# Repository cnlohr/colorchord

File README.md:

ColorChord
==========

Table of Contents
-----------------

- [ColorChord](#colorchord)
  - [Table of Contents](#table-of-contents)
  - [What is ColorChord?](#what-is-colorchord)
  - [Background](#background)
  - [Current State of Affairs](#current-state-of-affairs)
  - [ColorChord: Embedded](#colorchord-embedded)
- [Build Instructions](#build-instructions)
  - [Building ColorChord Embedded](#building-colorchord-embedded)
  - [Building with Linux](#building-with-linux)
  - [Building with Windows](#building-with-windows)
    - [clang](#clang)
    - [TCC](#tcc)
    - [MSYS2](#msys2)
  - [Using](#using)
  - [Additional Videos](#additional-videos)

What is ColorChord?
-------------------

Chromatic Sound to Light Conversion System.  It's really that simple.  Unlike so many of the sound responsive systems out there, ColorChord looks at the chromatic properties of the sound.  It looks for notes, not ranges.  If it hears an "E" it doesn't care what octave it's in, it's an E.  This provides a good deal more interesting patterns between instruments and music than would be available otherwise.

Background Video here:

ColorChord on an ESP8266:

More videos below!

Background
----------

Developed over many years, ColorChord 2 is now at the alpha stages.  ColorChord 2 uses the same principles as ColorChord 1.  A brief writeup on that can be seen here: http://cnlohr.blogspot.com/2010/11/colorchord-sound-lighting.html

The major differences in ColorChord 2 is the major rewrite to move everything back to the CPU and a multitude of algorithmic optimizations to make it possible to run on something other than the brand newest of systems.

Feuge in D Minor (ColorChord 2 running a strip of WS2812 LEDs):

ColorChord 2 running a voronoi diagram with Mayhem's Dr. Rocker

Current State of Affairs
------------------------

Currently, ColorChord 2 is designed to run on Linux or Windows.  It's not particularly tied to an architecture, but does pretty much need a dedicated FPU to achieve any decent performance.  Right now there aren't very many output options available for it.  The most interesting one used for debugging is a voronoi-diagram-like thing called "DisplayShapeDriver."

ColorChord: Embedded
--------------------

There is work on an embedded version of ColorChord, which avoids floating point operations anywhere in the output pipeline.  Though I have made efforts to port it to AVRs, it doesn't seem feasable to operate on AVRs without some shifty tricks which I'd like to avoid, so I have retargeted my efforts to 32-bit systems, such as the STM32F303, STM32F407, and (somehow) the ESP8266.  ColorChord Embedded uses a different codebase, located in the [embeddedcommon](/embeddedcommon) and distributed among the various embedded* folders.

Build Instructions
==================

Building ColorChord Embedded
----------------------------

The embedded version of Colorchord has a different build system than the desktop versions of Colorchord. See the build instructions for each of the supported embedded architectures in their respective folders

- [esp8266](embedded8266/README.md#build-instructions)
- [stm32f303](embeddedstm32f303/README.md)
- [stm32f407](embeddedstm32f407/) - TODO Add readme

Building with Linux
-----------------
From the linux terminal use `apt-get` to install the following packages for Debian/Ubuntu/Mint:
```
apt-get install build-essential libpulse-dev libasound2-dev libx11-dev libxext-dev libxinerama-dev libusb-1.0-0-dev libudev-dev
```

To get colorchord, type:

```
git clone --recurse-submodules https://github.com/cnlohr/colorchord
```
This will download the colorchord source code into the colorchord directory

You really want to be using colorchord2, so we need to move to it's build directory to compile the source code.
```
cd colorchord/colorchord2
```
To make colorchord, type:

```
make
```
Building with Windows
-------------------

There are 3 options available for building on Windows, clang, or TCC, MSYS2.
### clang
Start by [downloading](https://clang.llvm.org/) the clang compiler, and installing it.
You can also install using `winget` using the following command in PowerShell
```
winget install -e --id LLVM.LLVM
```

If you have the Windows SDK installed, you should not need to do any additional work.  
If you do not, you'll want to either [install it](https://developer.microsoft.com/en-US/windows/downloads/windows-11-sdk/) to get the official headers. Realistically, it's easyist to get the headers by installing Visual Studio Communitiy and selecting the C/C++ Desktop Application devlopment package and installing it from there [Visual Studio](https://visualstudio.microsoft.com/).

Once the Windows headers are installed run the clang batch script, and it should output to `colorchord2/colorchord.exe`.
```
./compile-clang.bat
```

### TCC
Start by [downloading TCC](http://savannah.nongnu.org/projects/tinycc/), and extracting it to `C:\tcc`.
You can put it anywhere you like, but the compile script defaults to this location. If you install 
to the default location, you can skip the next step.

Edit the batch script at `colorchord2/windows/compile.bat`:
- Edit line 17 (`CC`) to be the location where you put TCC. If there are spaces in the path, wrap the entire path in quotes.

Note that TCC is not able to use the Windows SDK, and as such using the unofficial headers is required, and automatically enabled when compiling with TCC. If you encounter issues, try the clang method above instead. TCC does not support open-gl rendering and is limited to software rendering.

### MSYS2
With either 64bit or 32bit [MSYS2](https://msys2.github.io/) installed, run the _MSYS2 MSYS_ launcher and use `pacman` to set up a MinGW32 toolchain, if you don't have one already:
```
pacman -S mingw-w64-i686-toolchain
```
If you see "`/mingw32 exists in filesystem`", you must temporarily rename or relocate the _mingw32.exe_ file at MSYS2's root folder level and try again. Restore _mingw32.exe_ before moving on.

Next, run the _MSYS2 MinGW 32bit_ launcher to access the toolchain. The previously launched _MSYS_ terminal can be closed.

To make colorchord, navigate to your working copy and type:
```
mingw32-make colorchord.exe
```

Using
-----

To run colorchord, use the following syntax:

```
./colorchord [config file, by default 'default.conf'] [any additional parameters]
```

If you edit default.conf while the program is running and resave it, it will use the settings in the newly saved file.

Note that the colorchord executable file is located in the colorchord2 directory in the colorchord repository. 

Additional Videos
-----------------

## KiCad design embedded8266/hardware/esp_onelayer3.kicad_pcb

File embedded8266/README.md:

#ESP8266 ColorChord

## WARNING THIS IS UNDER CONSTRUCTION

(based off of ESP8266 I2S WS2812 Driver)

This project is based off of the I2S interface for the mp3 player found here:
https://github.com/espressif/esp8266_mp3_decoder/

If you want more information about the build environment, etc.  You should
check out the regular WS2812 driver, found here: https://github.com/cnlohr/esp8266ws2812i2s

WARNING: This subproject is very jankey!  It's about stable, but I don't think it's quite there yet.

## Hardware Connection

Unfortunately the I2S Out (WS2812 in) pin is the same as RX1 (pin 25), which means if you are programming via the UART, it'll need to be unplugged any time you're testing.  The positive side of this is that it is a pin that is exposed on most ESP8266 breakout boards.

The audio data is taken from TOUT, but must be kept between 0 and 1V.

An option that has been thoroughly tested is for use with the 2019 MAGFest Swadge.  https://github.com/cnlohr/swadge2019

Audio portion:

## Notes

./makeconf.inc has a few variables that Make uses for building and flashing the firmware.
Most notably the location of the toolchain for the esp8266/85 on your system.
You should edit them according to your preferences or better add `export ESP_ROOT='/path/to/the/esp-open-sdk'` to your bashrc.

If you have problems with burning the firmware or transfering page data over network (`make netburn` or `make netweb`), you should try uncommenting

    OPTS += -DVERIFY_FLASH_WRITE

in `makeconf.inc`. This way the esp checks if the flash is written correctly.
Especially with some ESP-01 modules there has been a problem with the flash
not being written correctly.

## Build Instructions

To build colorchord for the esp8266, you first must install the development tools for the esp8266 so that you can compile the code and flash it to the device.

### Setup Toolchain
Follow the instructions in Charles' getting started video to install the toolchain (up until about 3:30 into the video).

The instructions shown in the video are from the [esp82xx repo](https://github.com/cnlohr/esp82xx) on github.

TLDR version: You should really watch the video and look at the other instructions though.
1. if you are on Windows you need to install WSL1 (Windows Subsystem for Linux version 1). 
2. Install Python2 and Make
3. Install pip (for Python 2)
4. Install pyserial (for Python 2)
5. Install Charles' prepackaged toolchain to the `~/esp8266` directory (`esp8266` directory in your home folder).
6. Set the `ESP_ROOT` environment variable in your `.profile` or `.bashrc` file. Check to see if one of these files exist (they are hidden by default), if one of them does exist, edit it adding the following line to the file.
```
export ESP_ROOT=$(HOME)/esp8266/esp-open-sdk
```

### Build Colorchord Embedded
At this point you should have your development toolchain set up, now we will download and install colorchord.

Start by cloning this git repository, in a terminal window use the command
```
git clone https://github.com/cnlohr/colorchord.git --recurse-submodules
```
This will download the source code for colorchord and all of its dependencies.

Next, move to the `embedded8266` directory so that we can compile the version of colorchord for the esp8266.
```
cd colorchord/embedded8266
```

Now we will need to build colorchord, this step will need to be done if you make any changes to the colorchord code.
```
make all
```
Hopefully the previous command completed without errors, if it did not, please refer to the [common problems](#common-problems) section. If all went well, there should be three binary files in your build directory `image.elf`, `image.elf-0x00000.bin`, and `image.elf-0x10000.bin`. You can check this with the command
```
ls -l image.elf*
```

### Flash to the ESP8266
Before flashing the program to the esp8266 it must be connected to the computer over a usb-to-serial connection and the correct port on the computer must be known. If using Windows (WSL) this will be the COM port shown by Windows Device Manager. For example, `COM4` in Windows will refer to `/dev/ttyS4` in WSL (See [2:35](https://youtu.be/LiKNRBIcGII?t=155) from the previously mentioned video). On a Linux machine it will most likely be `/dev/ttyUSB0`. The file determined here will specify the `PORT` value in later commands, so if you had `COM4`, then `PORT` would be `/dev/ttyS4`.

If this is your first time using the esp8266 module with colorchord run the following command.
```
PORT=<port value> make erase
PORT=<port value> make burnitall
```
These two commands erase the contents of esp8266 memory and flash the program (and some base files) to it.

If you have made some changes to colorchord and you want to test them use the command
```
PORT=<port_value> make burn
```
### Connect to the ESP8266
If all went well, the esp module should be broadcasting a wifi access point that you can connect to. Once that is done, you should be able to see the colorchord webpage dashboard at the ip address [192.168.4.1](http://192.168.4.1). That should be it! Enjoy using colorchord, and don't hesitate to reach out if you have any issues.

## Common Problems

**Under Construction**

If you experience any issues building colorchord embedded, please open an issue and we will try and work through it. I will try and keep this section up to date with relevant information.

**WSL Path Issues** 
Under WSL the default Windows environment paths are included. When building colorchord and the Windows User/System Path includes non Linux compatible characters (eg. spaces and parentheses like /Program Files (x86)) it will fail compililng.
An easy solution is to backup the Windows path variable, then deleting keys including spaces and parentheses and restarting WSL.

**Flash tool not using specified port**
WSL sometimes doesn't correctly use the environment variable that specifies the serial port. It needs to be changed in the user.cfg file in the /embedded8266 folder.

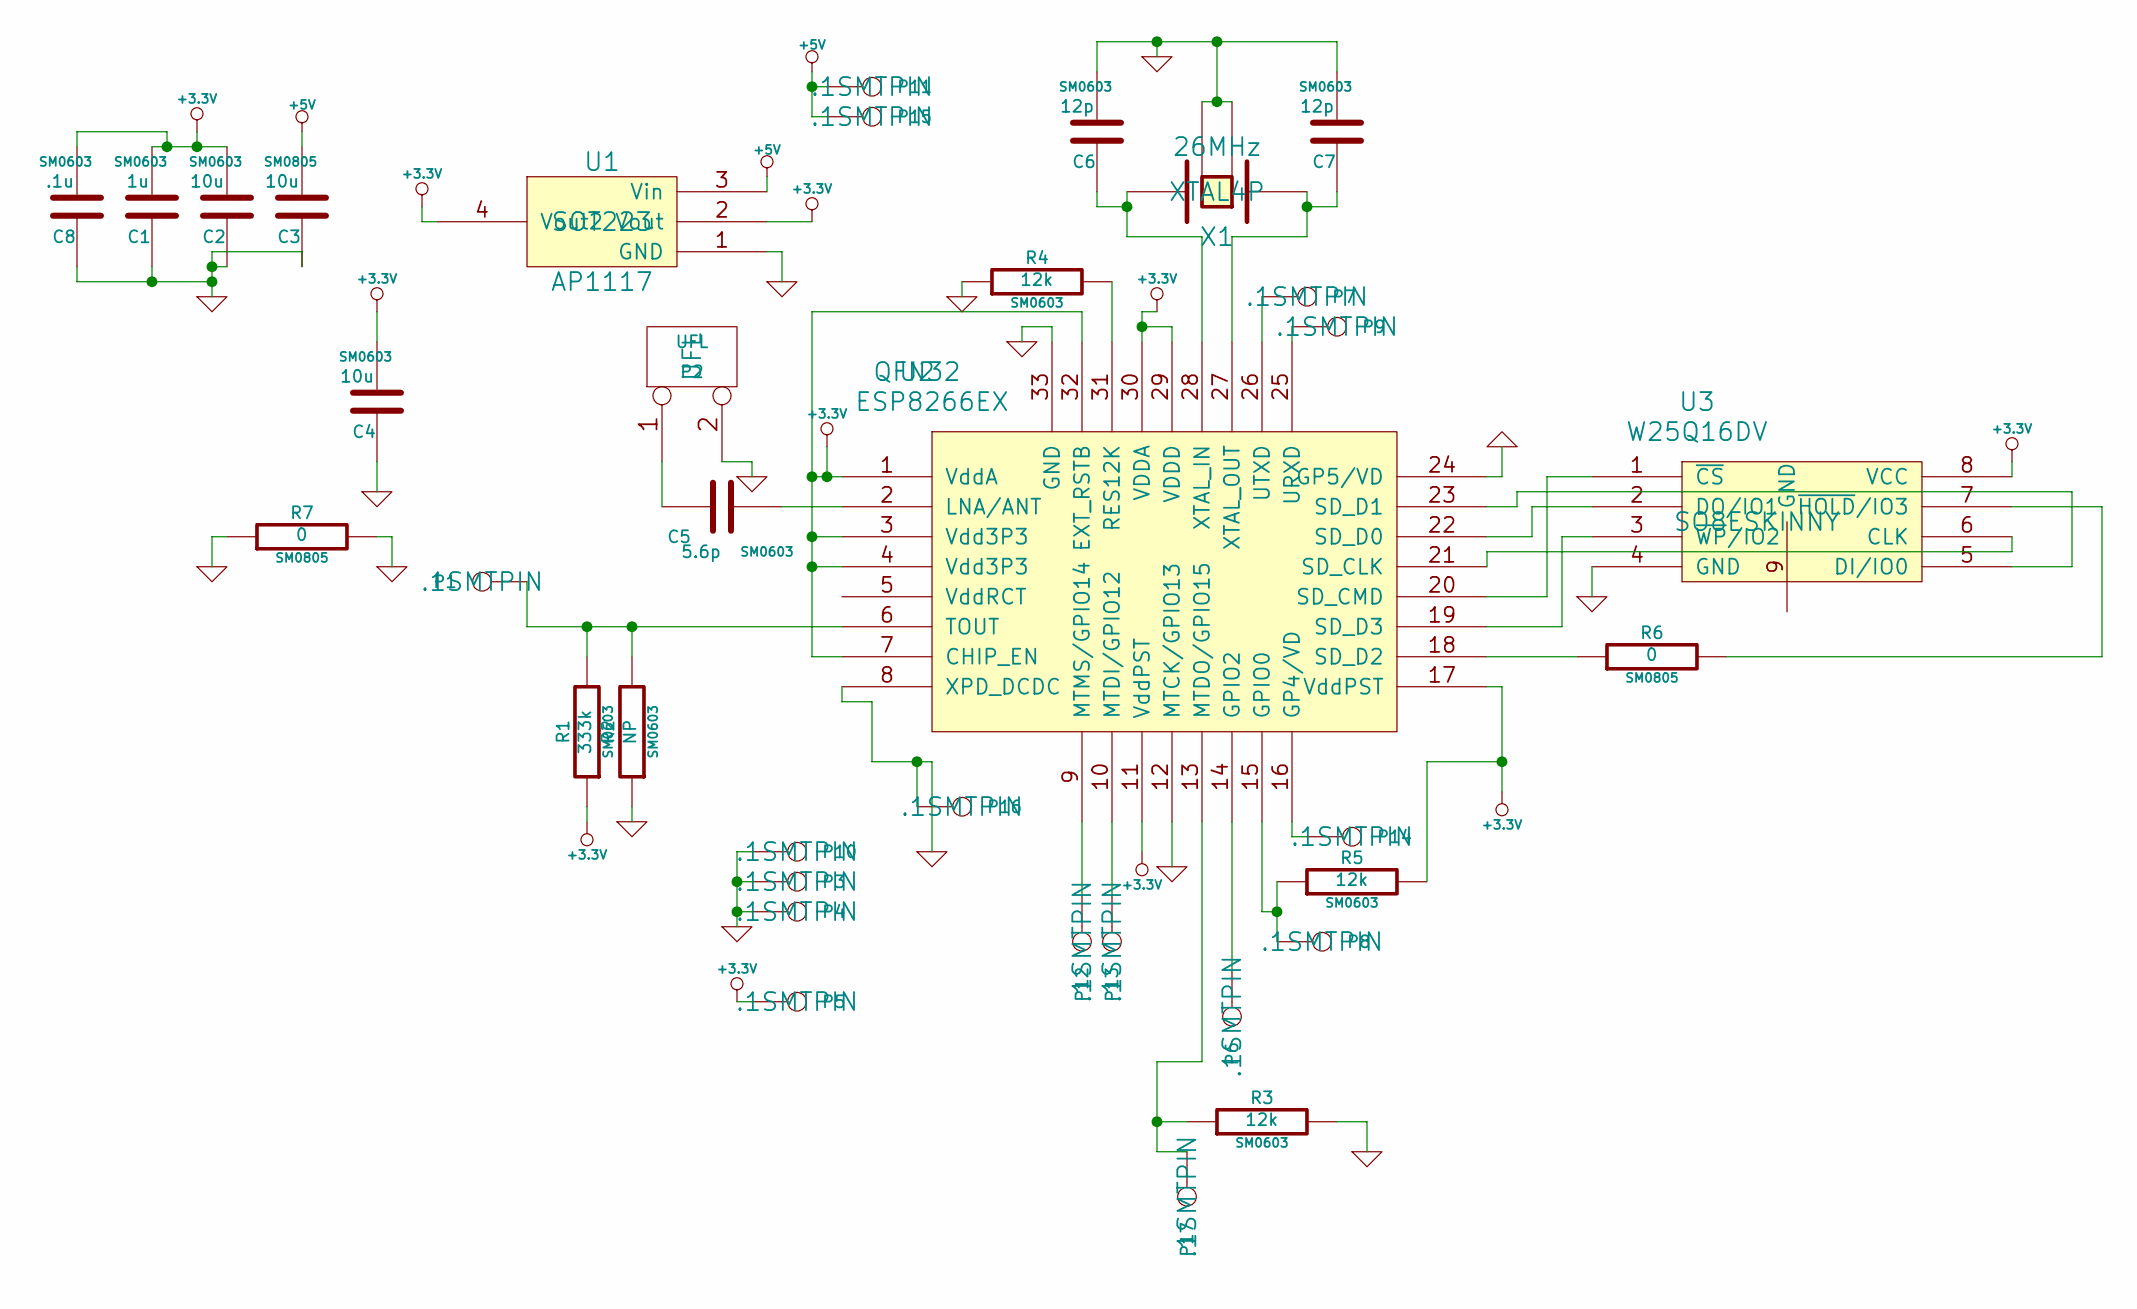
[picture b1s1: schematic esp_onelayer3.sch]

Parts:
C1: 1u; SM0603
C2, C4: 10u; SM0603
C3: 10u; SM0805
C5: 5.6p; SM0603
C6, C7: 12p; SM0603
C8: .1u; SM0603
P1: MIC; .1SMTPIN
P2: UFL
P3, P4, P10, P16: GND; .1SMTPIN
P5, P11, P15: 5V; .1SMTPIN
P6: GPIO2; .1SMTPIN
P7: UTX; .1SMTPIN
P8: GPIO0; .1SMTPIN
P9: URX; .1SMTPIN
P12: GPIO14; .1SMTPIN
P13: GPIO12; .1SMTPIN
P14: GPIO5; .1SMTPIN
P17: GPIO15; .1SMTPIN
R1: 333k; SM0603
R2: NP; SM0603
R3, R4, R5: 12k; SM0603
R6, R7: 0; SM0805
U1: AP1117; SOT223
U2: ESP8266EX; QFN32
U3: W25Q16DV; SO8ESKINNY
X1: 26MHz; XTAL4P

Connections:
+3.3V: C1.2, C2.2, C4.2, C8.2, P5.1, R1.1, R5.2, U1.2 (Vout), U1.4 (Vout2), U2.1 (VddA), U2.3 (Vdd3P3), U2.4 (Vdd3P3), U2.7 (CHIP_EN), U2.11 (VddPST), U2.17 (VddPST), U2.29 (VDDD), U2.30 (VDDA), U2.32 (EXT_RSTB), U3.8 (VCC)
+5V: C3.2, P11.1, P15.1, U1.3 (Vin)
GND: C1.1, C2.1, C3.1, C4.1, C6.2, C7.2, C8.1, P2.2 (PM), P3.1, P4.1, P10.1, P16.1, R2.1, R3.2, R4.1, R7.1, R7.2, U1.1 (GND), U2.8 (XPD_DCDC), U2.12 (MTCK/GPIO13), U2.24 (GP5/VD), U2.33 (GND), U3.4 (GND), X1.3 (GND), X1.4 (GND)
unnamed: P14.1, U2.16 (GP4/VD)
unnamed: P12.1, U2.9 (MTMS/GPIO14)
unnamed: P13.1, U2.10 (MTDI/GPIO12)
unnamed: R6.1, U2.18 (SD_D2)
unnamed: P7.1, U2.26 (UTXD)
unnamed: U2.21 (SD_CLK), U3.6 (CLK)
unnamed: U2.23 (SD_D1), U3.5 (DI/IO0)
unnamed: U2.22 (SD_D0), U3.2 (DO/IO1)
unnamed: U2.20 (SD_CMD), U3.1 (~CS)
unnamed: U2.19 (SD_D3), U3.3 (~WP~/IO2)
unnamed: R6.2, U3.7 (~HOLD~/IO3)
unnamed: P17.1, R3.1, U2.13 (MTDO/GPIO15)
unnamed: P1.1, R1.2, R2.2, U2.6 (TOUT)
unnamed: P8.1, R5.1, U2.15 (GPIO0)
unnamed: R4.2, U2.31 (RES12K)
unnamed: C5.2, U2.2 (LNA/ANT)
unnamed: C5.1, P2.1
unnamed: P6.1, U2.14 (GPIO2)
unnamed: P9.1, U2.25 (URXD)
unnamed: C7.1, U2.27 (XTAL_OUT), X1.1
unnamed: C6.1, U2.28 (XTAL_IN), X1.2

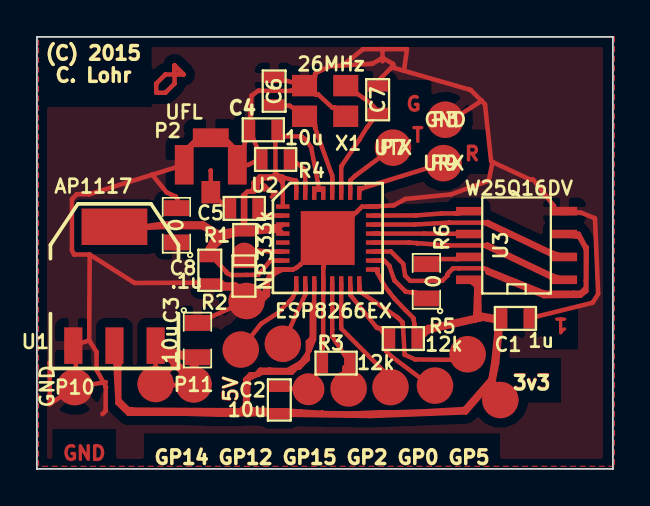
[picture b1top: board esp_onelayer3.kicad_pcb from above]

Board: 2 copper layers, 32.0 x 24.0 mm, 36 parts (0 on the bottom side), 24 nets.

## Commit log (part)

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2015-02-11 integer-based DFTs are working.
2015-02-11 update windows exe
2015-02-17 remove third clause
2015-04-02 okay, things are moving along quite well. Almost ready for my first test.
2015-04-03 update : use 11025 Hz. also, fix overflow bug with combining notes
2015-04-03 formalize boundary condition
2015-04-04 very close. Just cleanup to go.
2015-04-05 Add a lot of documentation, etc. for ColorChord Embedded.
2015-04-05 rearrange files some a few cleanups, too.
2015-06-04 I am on my way with this, but it's going slowly.
2015-06-26 add recording, etc. hooks.
2015-06-26 update from Merge
2015-06-30 Fix DMX plus actually stop recording add "White" function
2015-07-21 Add a STM32F407 version of EmbeddedColorChord
2015-07-21 update embeddedstm32f303 for use with a STM32F303
2015-07-22 clean up + Add utilities to the system.c/.h +Fix filter
2015-07-27 Update ColorChord for the ESP8266
2015-07-27 Move colorchord2 into its own folder, since colorchord embedded is its own thing.
2015-07-27 fix readme to make it less incorrect.
2015-07-29 Add tool to simulate LEDs
2015-07-29 Update ESP8266 version
2015-07-29 Update copyright noteices, etc.
2015-07-30 much further progress :)
    Able to have sustained and queued websockets connections at ~500 Hz. Commands pass over said connection.
2015-08-03 D'uh. Don't block interrupts on HTTP transfers!
2015-08-07 add better control for disabling flags on the screen for esp8266 wifi configuration
2015-08-08 Separate out code to handle web menu interface.
2015-08-09 Update with make-all-the-leds-the-same solo option.
2015-08-16 Update the 8266 stuff to my newest build.
2015-08-18 move update kicking
2015-08-28 Make colorchord work with W25Q40 memory, using the window of flash after the IRAM loaded section.
2016-03-18 Fix Windows build closes #7
2016-05-28 update aspects for having a overall equalizer/compressor
2016-06-06 Minor grammar fix! ;)
2016-07-21 Update for voice and input
2016-07-27 Fixes compatibility issues when making with OSX
2016-08-03 Clean up Makefiles
2016-08-03 Remove need for esptool-ck
2016-08-04 update with changes needed to operate some existing systems.
2016-08-04 Utilize web/Makefile from within the main Makefile (esp82XX)
2016-08-13 Some housekeeping fixes and fix a bug with "FR" that prevented it's functioning.
2016-08-13 move readme
2016-08-14 Fix typo
2016-08-14 fix lines for video headers
2016-08-14 update youtube videos
2016-08-15 Handle overhang when verifying flash
2016-08-18 Templateize index.html
2016-08-19 add .git to end of the git modules.
2016-08-19 Bump submodule
2016-08-20 Update exp82xx and make automatically get new submodules if needed
2016-08-23 Update to latest esp8266 and leverage new functionality.
    Also, uses less IRAM so it fits with SDK 1.5.4
2016-08-23 get rid of unneeded printf
2016-08-24 Bumped submodule
2016-08-27 push to forward
2016-10-08 Add WIN32 escape key
2016-10-09 Add instructions for building with Windows
2017-01-04 fix detached head
2017-02-12 Add notes about reading from correct monitor, don't spew data at the screen.
2017-02-12 add netlight8266
2017-02-16 Whoops forgot to turn on optimizations.
2017-04-13 Increased timeout for WifiDataTicker to 6 seconds.
    Scan For Stations fix. @pjmole
2017-04-14 Bug fix UpdateLinearLEDs, Improved UpdateRotatingLEDs
    UpdateLinearLEDs can now use LIN_WRAPAROUND while rotating LEDs
    UpdateRotatingLEDs now has code to have LED arc length proportional to amp2
    can have constant intensity or related to amp2
2017-04-15 12 seconds timeout for wifi scan select
    12 seconds timeout for wifi scan select
2017-04-16 Improved Output Options added Custom Command
2017-04-18 bubble sort, new params for custom commands
    SORT_NOTES is now controllable via web gui
    0 no sort, 1 sort inc by freq, 2 sort dec by amps, 3 by amps2
    LIN_WRAPAROUND now controllable via web gui 0 no, else yes
    ESP8266 now running much slower 32 HZ before 200 Hz
    not sure why. Code shouldn't be that much slower
2017-04-23 Improved spinning LEDs on peaks changes in embeddedout.c to shift computed display around the LED ring by using a modular frame count gFRAMECOUNT_MOD_SHIFT_INTERVAL and putting the shift into global 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
2017-04-25 UpdateAllSameLEDs() and UpdateRotatingLEDs() fixed to use NUM_LIN_LEDs
2017-04-25 Whoops! Undoing previous commit
2017-05-24 Add support for RGBY endpoints
2017-06-08 add file for irxmit
2017-06-22 forgot to set key on save.
2017-07-08 add hidapistuff
2017-07-16 Start ADC HPATimer only once. Makes for more stable collection of audio when connected to wifi (especially station mode). However the range of output from the ADC is truncated. TODO fix, or use syste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
2017-09-11 Fix Linux compile issues.
2017-09-11 Major progress to getting colorchord on Windows TCC
    Give it a shot. colorchord2/windows/compile.bat. I am having issues
    getting sound in.
2017-10-30 Fixed missing atoi + changed Init to InitColorChord
2018-05-08 Add SHM display for outputting directly to shared memory.
2018-05-08 Bump. Expose notes, too!
2018-05-08 bump makefile
2018-05-08 bump netlight
2018-05-08 Bump shmtest
2018-05-12 Typo on paragraph #038
2018-05-21 Make asynchronous operation better.
2018-05-21 Use semaphores for better performance.
2018-05-25 Add libudev-dev to dependencies
    Compilation would otherwise fail with
    ```
    hidapi.c:2161:21: fatal error: libudev.h: No such file or directory
    compilation terminated.
    <builtin>: recipe for target 'hidapi.o' failed
    make: *** [hidapi.o] Error 1
2018-07-03 Update default.conf
    Change to -1 to make it more universally functional on Windows.
2018-08-04 branch dev submodule esp82xx from bbkiwi
2018-10-11 Cleanup to understand
    Commented hpatimer.c
    Commented user_main.c
2018-10-11 Updated gitignore
2018-10-12 Removed bins
2018-10-14 Light refactoring
    Added custom_commands.h
    Added functions to check for and get
    Added hpaRunning to hpatimer.c, removed hpa_running from user_main.c
    Made sure variables have initial values
2018-11-09 Update with dodecahedron visualization
2018-11-18 update experimental branch
2018-11-18 Forgot to update the 303 folder
2018-11-18 Fix address!
2018-11-30 stab at the esp8266 port
2018-12-09 fix ALSA driver for Raspberry PI
2018-12-17 Update compile.bat
    add the "pause" command at the and so people who don't have tcc installed can read and find the issue
    or it just like a command window appear and disappear instantly
2019-03-17 cc2 Sort outdrivers.c imports
2019-03-17 Manual RawDraw Update
    Manually Merge / copy newest RawDraw code into the relevant files.
2019-03-17 cc2 add notefinder.h and parameters.h includes to outdrivers.h
    cc2 add notefinder.h and parameters.h includes to outdrivers.h
    Since those seem to be used in every outDriver and Display and shouldn't be separately included there each time.
2019-03-18 add Deconstruct mechanic to main.c
    add atExit() call to main method.
    This now calls the deconstruct method which can then call any other deconstruct / destroy method of anything else.
2019-03-18 finish deconstroction handling in main.c
2019-03-18 add CR LF to printfs in main.c
2019-04-07 progress on turbo8. Still not working - also new algebra problem found.
2019-04-27 working on 8bit turbo
2019-04-28 **Use this as reference point 1** Ok, this is actually pretty solid.
2019-04-28 Closing in.
2019-04-29 Further checkpoint - before optable rework
2019-04-29 8turbo is really turning into a real 8turbo
2019-04-29 add the paduk thing currently broken.
2019-05-22 Minor cleanup
2019-05-23 A squashed, should only change a few lines and no mucking about with submodules
2019-05-29 Fix ws2812_i2s.c to include ccconfig.h and explicitly invert literals to prevent warning
2019-06-18 Fix comment for removal of current defaults.
2019-06-18 making progress. reworking as I go.
2019-06-24 add support for the Impulse dance platform.
2019-07-06 Fixed bug when APPROXNORM == 1 is used when CCEMBEDDED is not defined (ie colorchord2)
2020-02-11 Update adc.c
    Please see the email I sent you.
2020-05-03 Update sound_android for use with rawdrawandroid.
2020-05-03 Cleanup extra printfs
2020-05-11 make ColorChord work on Android.
2020-05-11 cleanup when Android is suspending our app.
2020-05-11 Add ability for ColorChord-android to read external file.
2020-05-11 Allow other configuration schemes.
2020-05-11 Update submodule
2020-05-12 Fix app name
2020-05-12 Cleanup and improve back button behavior
2020-05-13 Fix build rev
2020-05-14 Added makefile to compile on Windows with clang
2020-05-14 Update Makefile to compile with clang
2020-05-14 Fix compile on non-android platforms.
2020-05-14 add docs
2020-05-14 Undo version bump
2020-05-15 Added script to compile with clang on Windows
2020-05-15 cnfa points to my repo
2020-05-15 this still needs some cleanup
2020-05-16 fix reversal in fread input arguments
2020-05-16 Added logging output
2020-05-16 Slightly change build scripts
2020-05-16 fixed bad URL
2020-05-17 Try supporting back to version 26.
2020-05-17 Updating CNFA
2020-05-17 Adding new required DLL reference, and updating CNFA
2020-05-17 TAG FOR RELEASE 8 Fix name of config file.
2020-05-17 Make a function to manually register parameters.
2020-05-17 Make clang not use windows headers
2020-05-18 Bump to new CNFA subsystem
2020-05-18 Switch search paths + update CNFA
2020-05-19 Edit the default configuration
2020-05-19 Update Windows build info in readme
2020-05-19 Ignoring clang output
2020-05-20 Modify build scripts
2020-05-20 Add more comments to the default configuration
2020-05-20 Oops, that could have been embareassing.
2020-05-20 Clarifying config comments
2020-05-21 Fix TCC being dumb
2020-05-21 Fix CNFA initilization call.
2020-05-21 Slightly change default config
2020-05-21 Bump ColorChord on Windows
2020-05-22 Update swapped order of ops in CNFA.
2020-05-22 switch out cc for $(CC) in Makefile
2020-07-06 Fix flipped argument order and update CNFA
2020-08-05 Make STM32F303x6/x8 vs xB/xC
2020-08-05 Update colorchord on the STM32f303
2020-09-22 Make netlight dmx loop
2020-10-03 Allow building on non-Linux Unix systems.
    - Use pkg-config to find required libraries and include paths.
    - Only include extra Linux libraries on Linux.
    - Add libusb fallback code to hidapi.c
2020-11-01 Fix bug(?) if dft.c
2021-01-01 Fixing rare out-of-bounds crash
2021-02-13 Set default ESP_ROOT -ESP_ROOT=~/esp8266/esp-open-sdk
2021-03-13 Update .clang-format with more rules
2021-03-13 Clean up main.c
2021-03-13 Fix some allignment issues noticed in github
2021-03-13 Fix allignment issue
2021-04-29 bump CNFA submodule
    Fix CNFA driver not being loaded with clang on Windows [Issue 121](https://github.com/cnlohr/colorchord/issues/121)
    This was caused by improper #ifdef guards on driver initilization code
    in CNFA.
2021-05-22 Fix formatting issues
2021-06-03 Fix Windows build
2021-06-05 Updated devrecord - Made windows loopback device the default - Added instructions on how to do the same on Linux
2021-06-05 Slight update to the build instructions
2021-06-05 Remove old, dead, code
2021-06-05 Bump rawdraw version
2021-06-08 Update colorchord binary
2022-09-07 Update LICENSE
2022-10-22 All files included in Windows build - Displays that only work on linux have a compile guard
2022-10-22 Remove FPS counter on command line - Don't show debug info by default - Other minor formatting changes
2022-10-22 Build and cleanup colorchord-opengl by default. - Remove binary from tracked files
2022-11-12 Fix build on unusual version of mingw.
2022-12-06 Fixing cnfa module referencing nonexistant commit
2023-01-20 Add note about careful selection of samplerate
2023-01-20 Move really lowspec tests over.
2023-01-20 A few tweaks.
2023-07-29 Update clang to not require Windows SDK.
2023-08-27 Update README.md
    instruction to resolve common issues
2025-01-31 Progress, still has some bugs, like needing to rotate, and discontinuities on shifting Q but other than that ready to go.
